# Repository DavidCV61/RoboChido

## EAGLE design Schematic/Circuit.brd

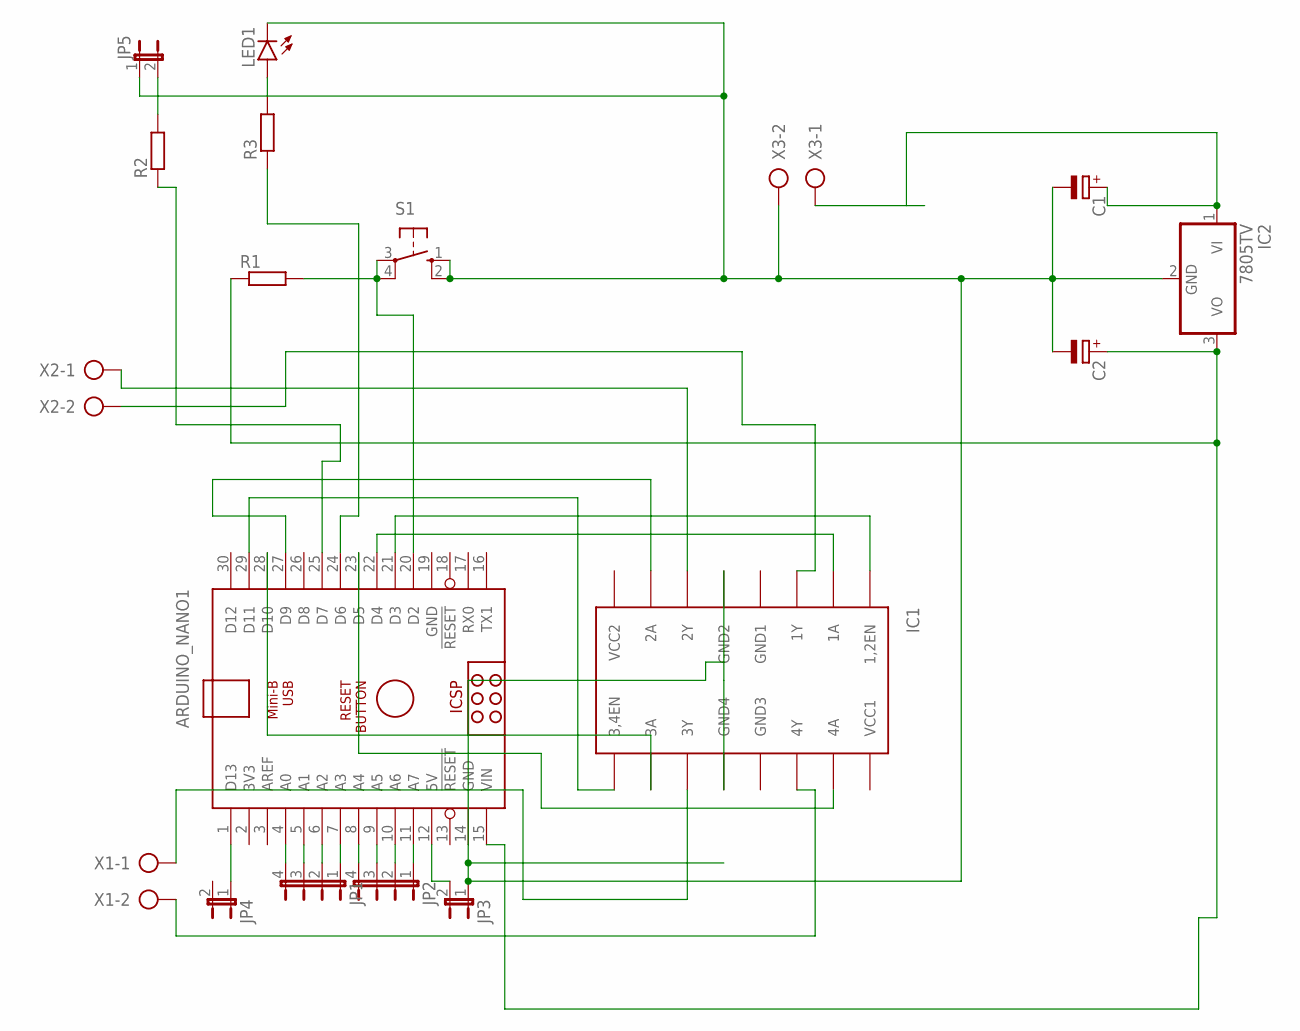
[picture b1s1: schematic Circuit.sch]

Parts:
ARDUINO_NANO1: ARDUINO_NANO
C1, C2: CPOL-EUE2.5-6; E2,5-6
IC1: L293D; DIL16
IC2: 7805TV; TO220V
JP1, JP2: JP4E; JP4
JP3, JP4, JP5: JP1E; JP1
LED1: LED5MM
R1, R2, R3: R-EU_0207/12; 0207/12
S1: 10-XX; B3F-10XX
X1, X2, X3: AK500/2

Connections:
GND: ARDUINO_NANO1.19 (GND)
GND1: IC1.4 (GND1)
GND3: IC1.13 (GND3)
unnamed: ARDUINO_NANO1.4 (A0), JP1.4
unnamed: ARDUINO_NANO1.5 (A1), JP1.3
unnamed: ARDUINO_NANO1.6 (A2), JP1.2
unnamed: ARDUINO_NANO1.7 (A3), JP1.1
unnamed: ARDUINO_NANO1.8 (A4), JP2.4
unnamed: ARDUINO_NANO1.9 (A5), JP2.3
unnamed: ARDUINO_NANO1.10 (A6), JP2.2
unnamed: ARDUINO_NANO1.11 (A7), JP2.1
unnamed: ARDUINO_NANO1.12 (5V), JP3.2
unnamed: ARDUINO_NANO1.24 (D6), R3.1
unnamed: ARDUINO_NANO1.1 (D13), JP4.1
unnamed: ARDUINO_NANO1.21 (D3), IC1.1 (1,2EN)
unnamed: ARDUINO_NANO1.22 (D4), IC1.2 (1A)
unnamed: ARDUINO_NANO1.27 (D9), IC1.7 (2A)
unnamed: ARDUINO_NANO1.29 (D11), IC1.9 (3,4EN)
unnamed: ARDUINO_NANO1.23 (D5), IC1.15 (4A)
unnamed: ARDUINO_NANO1.28 (D10), IC1.10 (3A)
unnamed: IC1.11 (3Y), X1.1
unnamed: IC1.14 (4Y), X1.2
unnamed: IC1.6 (2Y), X2.1
unnamed: IC1.3 (1Y), X2.2
unnamed: C1.+, IC2.1 (VI), X3.1
unnamed: ARDUINO_NANO1.15 (VIN), C2.+, IC2.3 (VO), R1.1
unnamed: ARDUINO_NANO1.14 (GND), C1.-, C2.-, IC1.5 (GND2), IC1.12 (GND4), IC2.2 (GND), JP3.1, JP5.1, LED1.K (C), S1.1 (S), S1.2 (S1), X3.2
unnamed: ARDUINO_NANO1.20 (D2), R1.2, S1.3, S1.4 (P1)
unnamed: LED1.A, R3.2
unnamed: ARDUINO_NANO1.25 (D7), R2.1
unnamed: JP5.2, R2.2
VCC1: IC1.16 (VCC1)
VCC2: IC1.8 (VCC2)

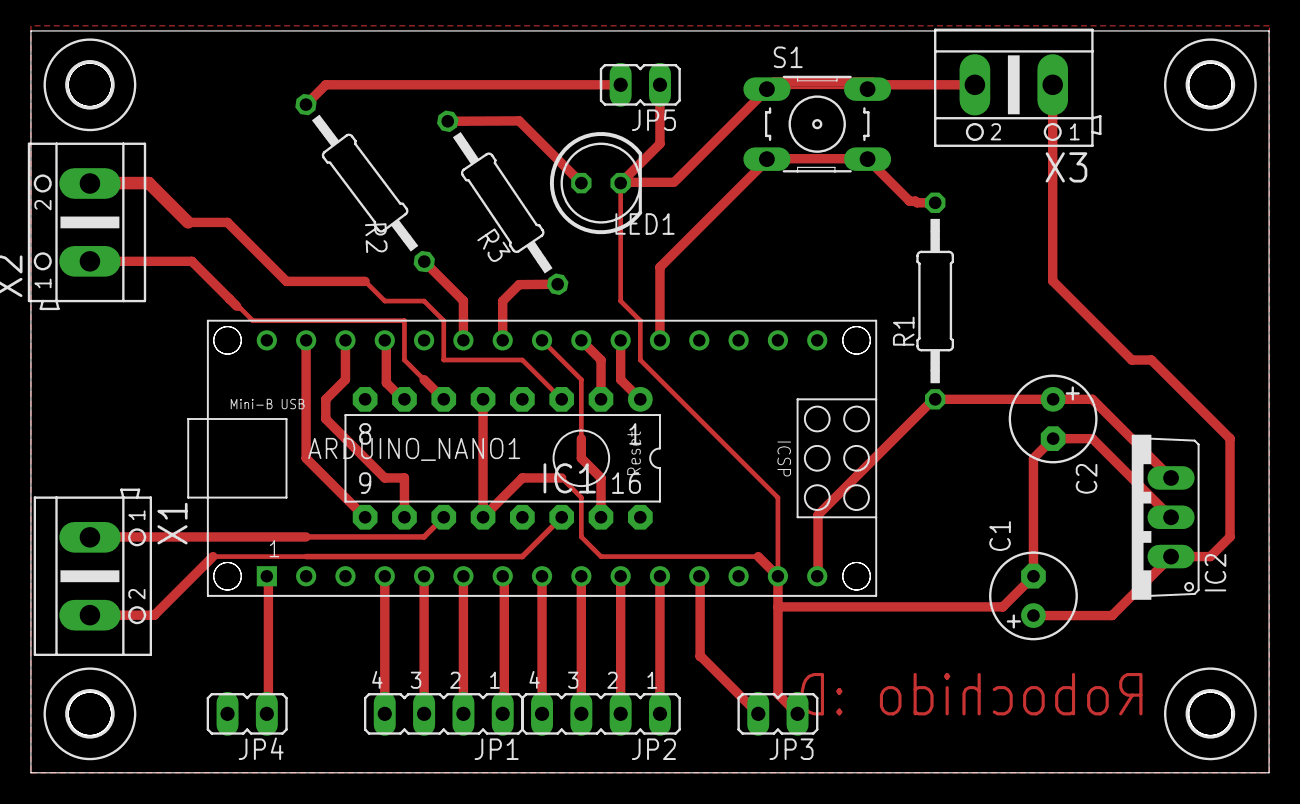
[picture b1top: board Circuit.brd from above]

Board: 2 copper layers, 80.0 x 47.9 mm, 22 parts (0 on the bottom side), 28 nets.

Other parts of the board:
U$1, U$2, U$3, U$4: 2,8
